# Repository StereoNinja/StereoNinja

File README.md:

# Stereo Ninja

Stereo Ninja is a DIY digital stereo microscope

# Overview

If you ever soldered SMT components or looked for issues on one of those tiny PCBs, you know that using a good microscope helps a lot, especially if it is a stereo microscope. But a good stereo microscope comes with a hefty price tag, so it's not for everyone. A cheap alternative is using a "usb microscope", but then of course you do not have stereo vision.

Our idea is to combine best of both worlds. Having proper stereoscopic view on your work piece and using relatively cheap digital components for archiving that. If you already have a 3D capable monitor, you only need a pair of cameras with suitable optics and some electronics for combining the two video streams into a single one that your monitor understands. We are using a Raspberry Pi for that (what else? ;-)).

# Details

Stereo Ninja is a dual camera setup for stereoscopic microscopy. The heart of the project is a Raspberry Pi. To be precise, you need a Raspberry Pi 3 or 4 Compute Module and a breakout board that gives you access to both MIPI CSI camera input ports the chip set offers, but is not available at the standard Raspberry Pi 3 or 4 versions. Then of course, you need 2 RaspberryPi-compatible cameras with suitable lenses. Our microscope setup is meant for electronics work, so we chose lenses that do not give you that much of a magnification, but permits an adequate lens-object distance for conveniently working under it. Then of course, you need a 3D monitor for displaying the stereoscopic view on your workpiece. We chose a fast 3D-capable gaming monitor with shutter goggles. Finally, a nice stand for you camera is needed.

All these components allow a selection from a variety of choices. We'll try to come up with a good recommendation on what you would want to get, but it is also possible to mix and match these parts (makes sense e.g. when you already own e.g. a 3d monitor). We'll try to list many of these combinations and document how to get them working. If you try a new lens/camera/board/monitor, let us know how it worked for you!

Here's Uli giving you a quick demo of the Stereo Ninja:

# Where do I get more information?

This repository is work in progress. More info about what we did so far can be found on [hackaday.io](https://hackaday.io/project/180044-stereo-ninja)

# Roadmap

## Beta release (work in progress)

* Hardware: 
  * Raspberry Pi CM4, Waveshare CM IO Board
  * 2x Raspberry Pi v1 camera + custom lens
  * connection of camera module with Pi with single cable 
* Software
  * Special version of raspivid
  * Outputs side-by-side stereo mode video to be used with 3d monitor
  * User can switch view (digital zoom on/off)
* Documentation
  * BOM
  * Assembly guide

### Todos Beta Release

- [x] Proof-of-Concept: StereoPi + Raspi3 Compute Module: real-time video stream to 3d monitor
- [x] Tests with CM4 (Raspi4 Compute Module)
- [x] Camera module: Dual-camera mount and enclosure (3d printed)
- [x] Camera module: print + test
- [x] Choose cable type for camera module to Pi connection
- [x] Camera board: circuit design 
- [x] Camera board: PCB layout
- [x] Camera board: assembly + testing
- [ ] Finalize Bill of Material
- [ ] Assembly guide / setup instructions

### Todos Release

- [ ] Software: switching between mode 5 (full sensor) and mode 1 (digital zoom)
- [ ] latency optimization: test different software setups, measure latency
- [ ] Select more suitable lenses

## Future feature ideas

* integrate LED lighting
* add buttons e.g. for zooing at camera
* Evaluate possibility the use of standard (non 3D) monitors by generating the signals for the shutter glasses ourselves
* Integrate polarization filter
* software: enable highres photo snapshots
* software: enable streaming/recording
* try to use Raspi v2 compatible cameras (3rd party IMX219 cam with M12 lens mount), see [issue #1](https://github.com/StereoNinja/StereoNinja/issues/1)
* try to use Raspi HQ compatible cameras (3rd party IMX477 cam with M12 lens mount), see [issue #2](https://github.com/StereoNinja/StereoNinja/issues/2)
* smart zoom: zoom into region where your solder tip or test lead points to
* enable video overlay (display PCB info like BOM directly on screen)
* Kicad integration 
* AR mode (e.g. for part placement on PCBs, highlighting tracks, etc)

# FAQ

### I want to build one! Where is the BOM etc?

Hang on for a bit longer. We are preparing the first release. We will have a BOM and all the design files you need by then.

### Do I need a 3D monitor?

Yes. At least for the first version. We are planning a side project that would allow using standard monitors by driving shutter glasses with our own control electronics. But no work has been done on this yet.

### How can I contribute?

At the moment the development is done by a team located at the FabLab München. We are currently not prepared for onboarding 
people who cannot join our in-person meetings. But there are some topics where development could be done quite independently, 
e.g. support for standard monitors (see previous FAQ) or software support for the new Raspberry Pi camera infrastructure.
In any case, if you interested in joining efforts, get in touch!

### How can I get in touch with you?

Drop us an email: stereoninja@fablab-muenchen.de

We are also on twitter: https://twitter.com/_stereoninja

---

Stereo Ninja is a project by FabLab München e.V. It is part of the [MakerTools project](https://wiki.fablab-muenchen.de/pages/viewpage.action?pageId=126815075), which is sponsored by the Federal Ministry of Education and Research.

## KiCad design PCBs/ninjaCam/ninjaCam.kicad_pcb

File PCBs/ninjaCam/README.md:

Empty directory for first Version for "ninjaCam" PCB
Use on your own risk - could create some magic smoke or just not working 

Should be pluged on Waveshare's Mini Base Board for Raspberry CM4. See also Mechanical/Cad files for assembly. 

License of PCB in this directory:
CERN-OHL-W

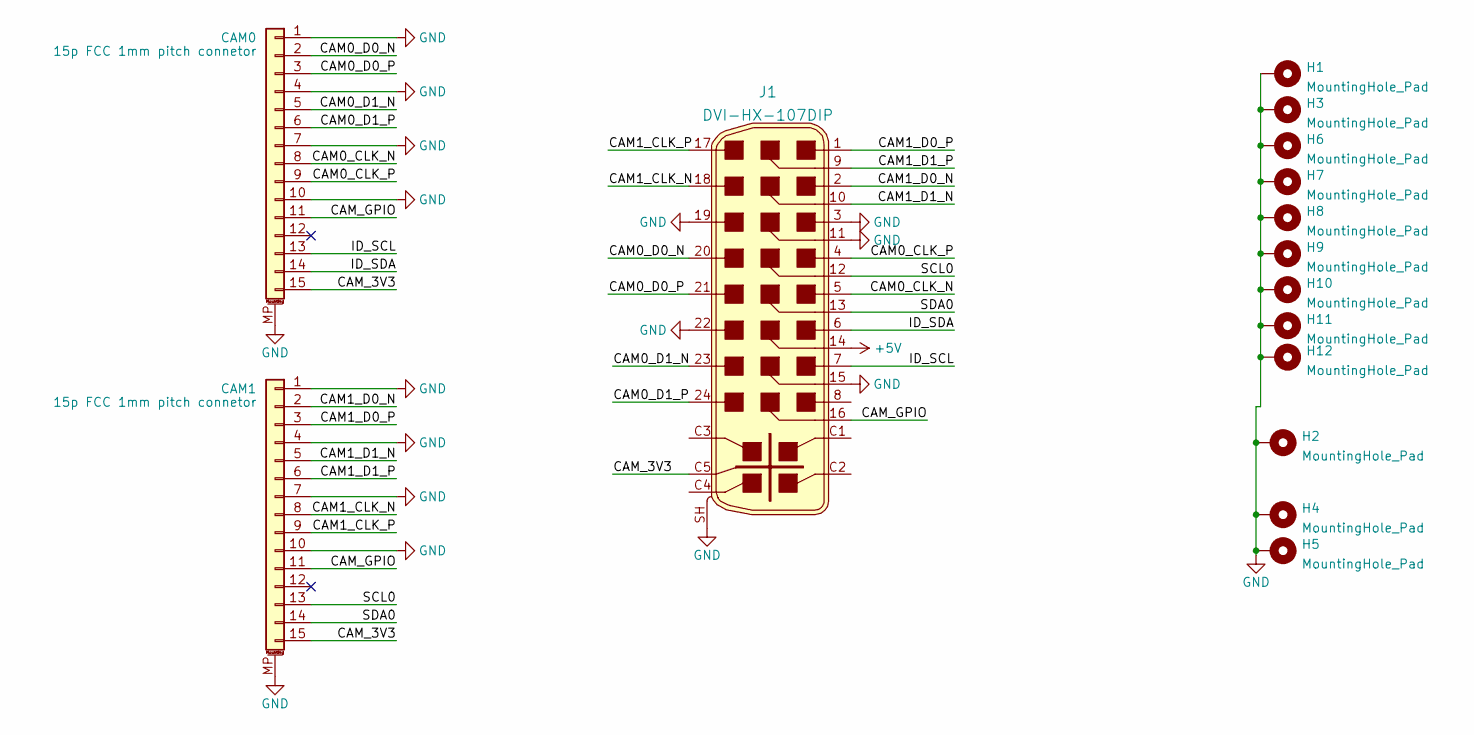
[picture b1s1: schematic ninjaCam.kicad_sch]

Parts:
CAM0, CAM1: 15p FCC 1mm pitch connetor; TE_1-84952-5_1x15-1MP_P1.0mm_Horizontal
H1, H3, H6, H7, H8, H9, H10, H11, H12: MountingHole_Pad; WA-SMSI_9774010360
H2, H4, H5: MountingHole_Pad; MountingHole_3.2mm_M3_Pad_Via
J1: DVI-HX-107DIP; DVI_Female_74320-9010; MPN DVI-HX-107DIP; LCSC# C2936242

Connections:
+5V: J1.14
/CAM0_CLK_N: CAM0.8, J1.5
/CAM0_CLK_P: CAM0.9, J1.4
/CAM0_D0_N: CAM0.2, J1.20
/CAM0_D0_P: CAM0.3, J1.21
/CAM0_D1_N: CAM0.5, J1.23
/CAM0_D1_P: CAM0.6, J1.24
/CAM1_CLK_N: CAM1.8, J1.18
/CAM1_CLK_P: CAM1.9, J1.17
/CAM1_D0_N: CAM1.2, J1.2
/CAM1_D0_P: CAM1.3, J1.1
/CAM1_D1_N: CAM1.5, J1.10
/CAM1_D1_P: CAM1.6, J1.9
/CAM_3V3: CAM0.15, CAM1.15, J1.C5
/CAM_GPIO: CAM0.11, CAM1.11, J1.16
/ID_SCL: CAM0.13, J1.7
/ID_SDA: CAM0.14, J1.6
/SCL0: CAM1.13, J1.12
/SDA0: CAM1.14, J1.13
GND: CAM0.1, CAM0.4, CAM0.7, CAM0.10, CAM0.MP (MountPin), CAM1.1, CAM1.4, CAM1.7, CAM1.10, CAM1.MP (MountPin), H1.1, H2.1, H3.1, H4.1, H5.1, H6.1, H7.1, H8.1, H9.1, H10.1, H11.1, H12.1, J1.3, J1.11, J1.15, J1.19, J1.22, J1.SH

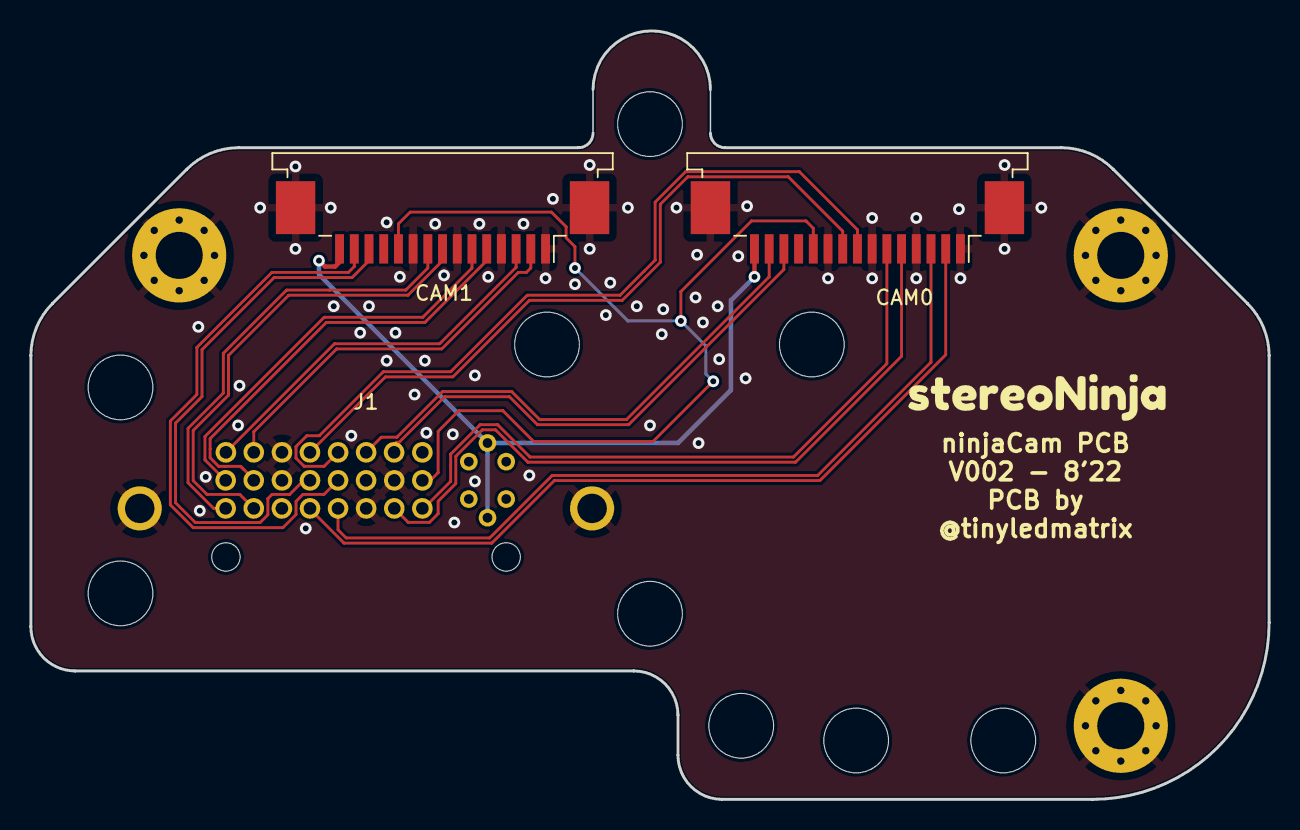
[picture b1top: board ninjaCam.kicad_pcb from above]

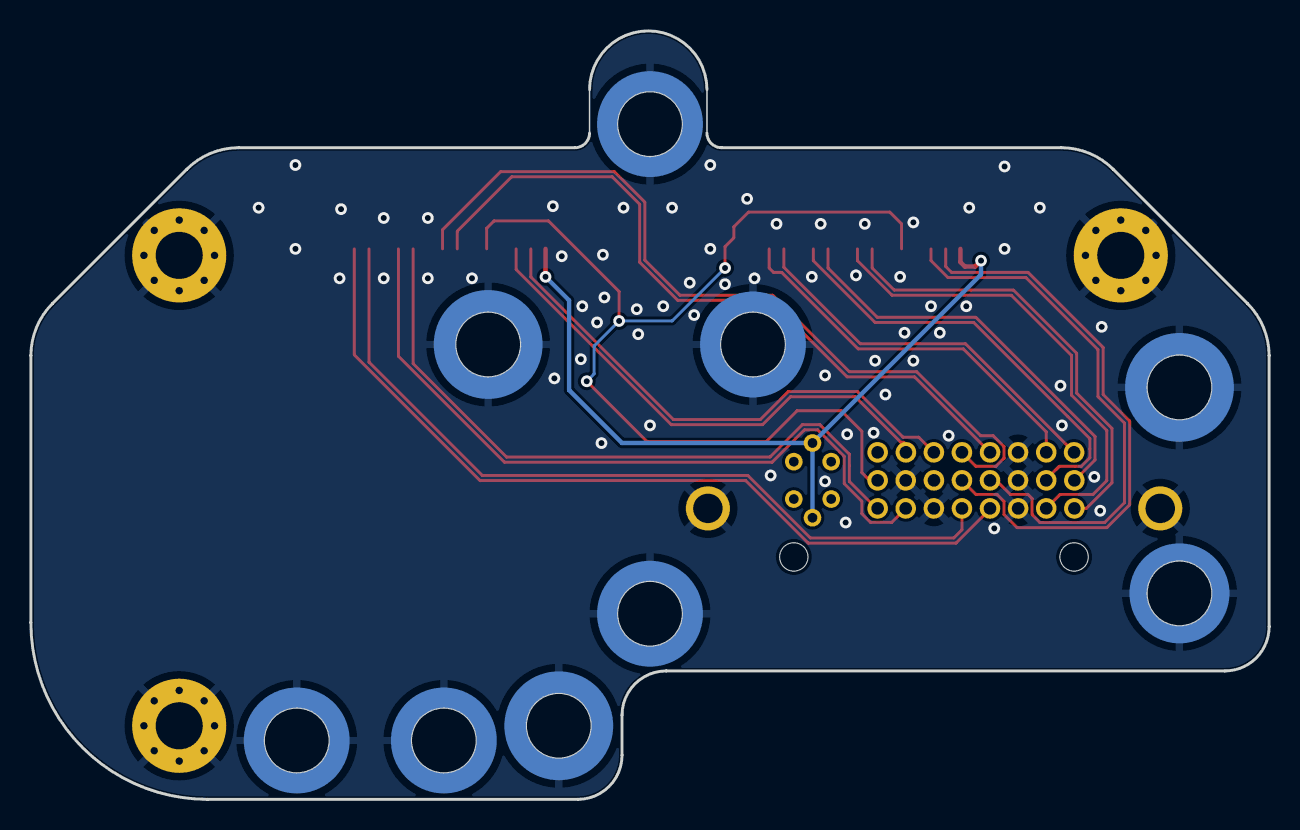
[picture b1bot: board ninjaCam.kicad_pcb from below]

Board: 2 copper layers, 84.2 x 52.2 mm, 16 parts (9 on the bottom side), 19 nets.

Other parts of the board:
kibuzzard-62BCCBE5: G***; kibuzzard-62BCCBE5

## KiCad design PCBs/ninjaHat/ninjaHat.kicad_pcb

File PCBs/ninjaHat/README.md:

Untested first Version for "ninjaHat" PCB
Use on your own risk - could create some magic smoke or just not working 

Should be pluged on Waveshare's Mini Base Board for Raspberry CM4. See also Mechanical/Cad files for assembly. 

License of PCB in this directory:
CERN-OHL-W

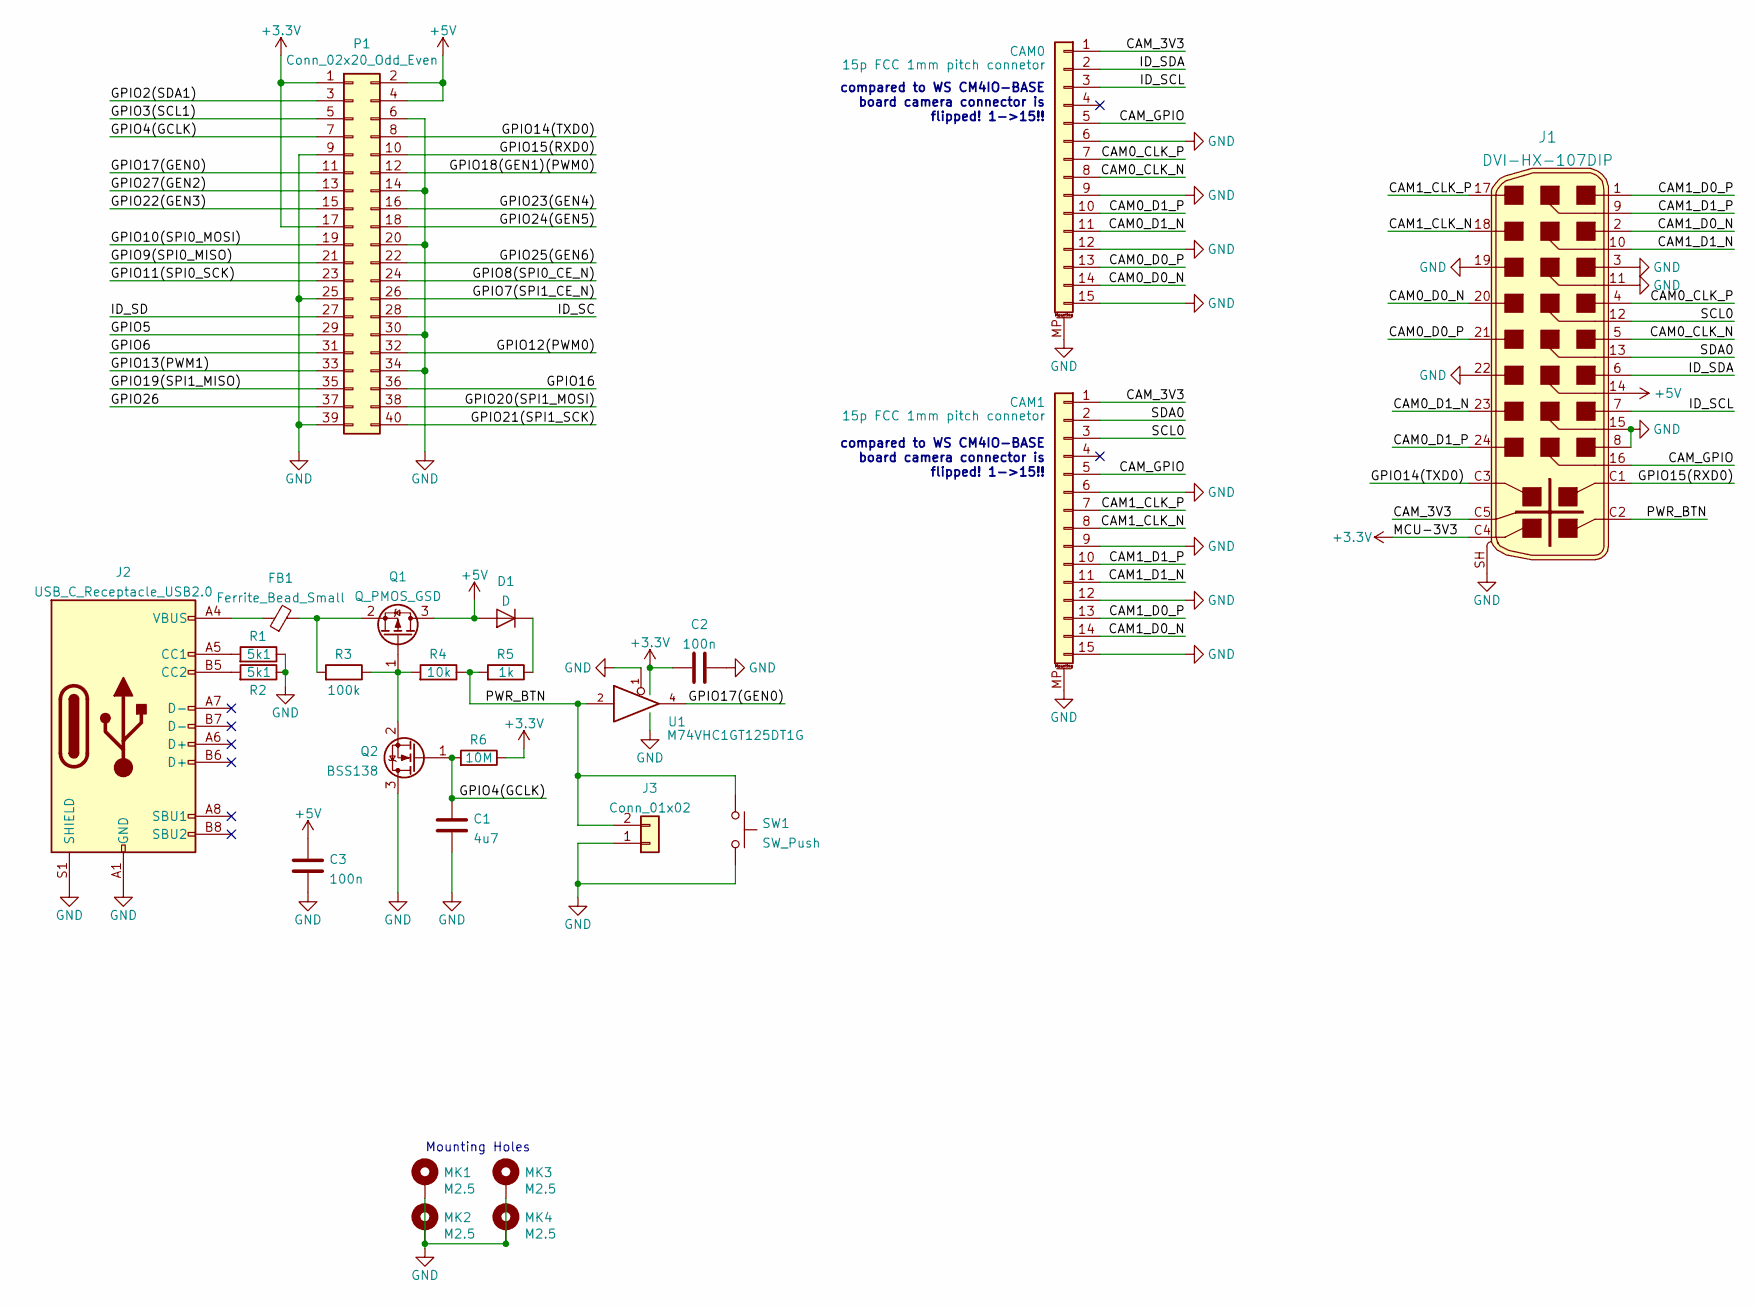
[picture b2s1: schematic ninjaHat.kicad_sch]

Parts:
C1: 4u7; C_0603_min
C2, C3: 100n; C_0603_min
CAM0, CAM1: 15p FCC 1mm pitch connetor; TE_1-84952-5_1x15-1MP_P1.0mm_Horizontal
D1: D; D_SOD-323
FB1: Ferrite_Bead_Small; L_0603_min
J1: DVI-HX-107DIP; DVI_Female_74320-9010; MPN DVI-HX-107DIP; LCSC# C2936242
J2: USB_C_Receptacle_USB2.0; USB_C_Receptacle_GT-USB-7010
J3: Conn_01x02; PinHeader_1x02_P2.54mm_Vertical
MK1, MK2, MK3, MK4: M2.5; MountingHole_3.2mm_M3_Pad_Via
P1: Conn_02x20_Odd_Even; PinSocket_2x20_P2.54mm_Vertical
Q1: Q_PMOS_GSD; SOT-23
Q2: BSS138; SOT-23
R1, R2: 5k1; R_0603_min
R3: 100k; R_0603_min
R4: 10k; R_0603_min
R5: 1k; R_0603_min
R6: 10M; R_0603_min
SW1: SW_Push; SW_PUSH_6mm
U1: M74VHC1GT125DT1G; TSOP-5_1.65x3.05mm_P0.95mm

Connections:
+3V3: C2.1, J1.C4, P1.1, P1.17, R6.1, U1.5 (VCC)
+5V: C3.2, D1.2 (A), J1.14, P1.2, P1.4, Q1.3 (D)
/CAM0_CLK_N: CAM0.8, J1.5
/CAM0_CLK_P: CAM0.7, J1.4
/CAM0_D0_N: CAM0.14, J1.20
/CAM0_D0_P: CAM0.13, J1.21
/CAM0_D1_N: CAM0.11, J1.23
/CAM0_D1_P: CAM0.10, J1.24
/CAM1_CLK_N: CAM1.8, J1.18
/CAM1_CLK_P: CAM1.7, J1.17
/CAM1_D0_N: CAM1.14, J1.2
/CAM1_D0_P: CAM1.13, J1.1
/CAM1_D1_N: CAM1.11, J1.10
/CAM1_D1_P: CAM1.10, J1.9
/CAM_3V3: CAM0.1, CAM1.1, J1.C5
/CAM_GPIO: CAM0.5, CAM1.5, J1.16
/GPIO2(SDA1): P1.3
/GPIO3(SCL1): P1.5
/GPIO4(GCLK): C1.1, P1.7, Q2.1 (G), R6.2
/GPIO5: P1.29
/GPIO6: P1.31
/GPIO7(SPI1_CE_N): P1.26
/GPIO8(SPI0_CE_N): P1.24
/GPIO9(SPI0_MISO): P1.21
/GPIO10(SPI0_MOSI): P1.19
/GPIO11(SPI0_SCK): P1.23
/GPIO12(PWM0): P1.32
/GPIO13(PWM1): P1.33
/GPIO14(TXD0): J1.C3, P1.8
/GPIO15(RXD0): J1.C1, P1.10
/GPIO16: P1.36
/GPIO17(GEN0): P1.11, U1.4
/GPIO18(GEN1)(PWM0): P1.12
/GPIO19(SPI1_MISO): P1.35
/GPIO20(SPI1_MOSI): P1.38
/GPIO21(SPI1_SCK): P1.40
/GPIO22(GEN3): P1.15
/GPIO23(GEN4): P1.16
/GPIO24(GEN5): P1.18
/GPIO25(GEN6): P1.22
/GPIO26: P1.37
/GPIO27(GEN2): P1.13
/ID_SC: P1.28
/ID_SCL: CAM0.3, J1.7
/ID_SD: P1.27
/ID_SDA: CAM0.2, J1.6
/PWR_BTN: J1.C2, J3.2, R4.1, R5.2, SW1.1, U1.2
/SCL0: CAM1.3, J1.12
/SDA0: CAM1.2, J1.13
GND: C1.2, C2.2, C3.1, CAM0.6, CAM0.9, CAM0.12, CAM0.15, CAM0.MP (MountPin), CAM1.6, CAM1.9, CAM1.12, CAM1.15, CAM1.MP (MountPin), J1.3, J1.8, J1.11, J1.15, J1.19, J1.22, J1.SH, J2.A1 (GND), J2.A12 (GND), J2.B1 (GND), J2.B12 (GND), J2.S1 (SHIELD), J3.1, MK1.1, MK2.1, MK3.1, MK4.1, P1.6, P1.9, P1.14, P1.20, P1.25, P1.30, P1.34, P1.39, Q2.3 (D), R1.1, R2.1, SW1.2, U1.1, U1.3 (GND)
unnamed: D1.1 (K), R5.1
unnamed: FB1.1, J2.A4 (VBUS), J2.A9 (VBUS), J2.B4 (VBUS), J2.B9 (VBUS)
unnamed: FB1.2, Q1.2 (S), R3.2
unnamed: J2.A5 (CC1), R1.2
unnamed: J2.B5 (CC2), R2.2
unnamed: Q1.1 (G), Q2.2 (S), R3.1, R4.2

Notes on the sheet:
compared to WS CM4IO-BASE board camera connector is flipped! 1->15!!
Mounting Holes

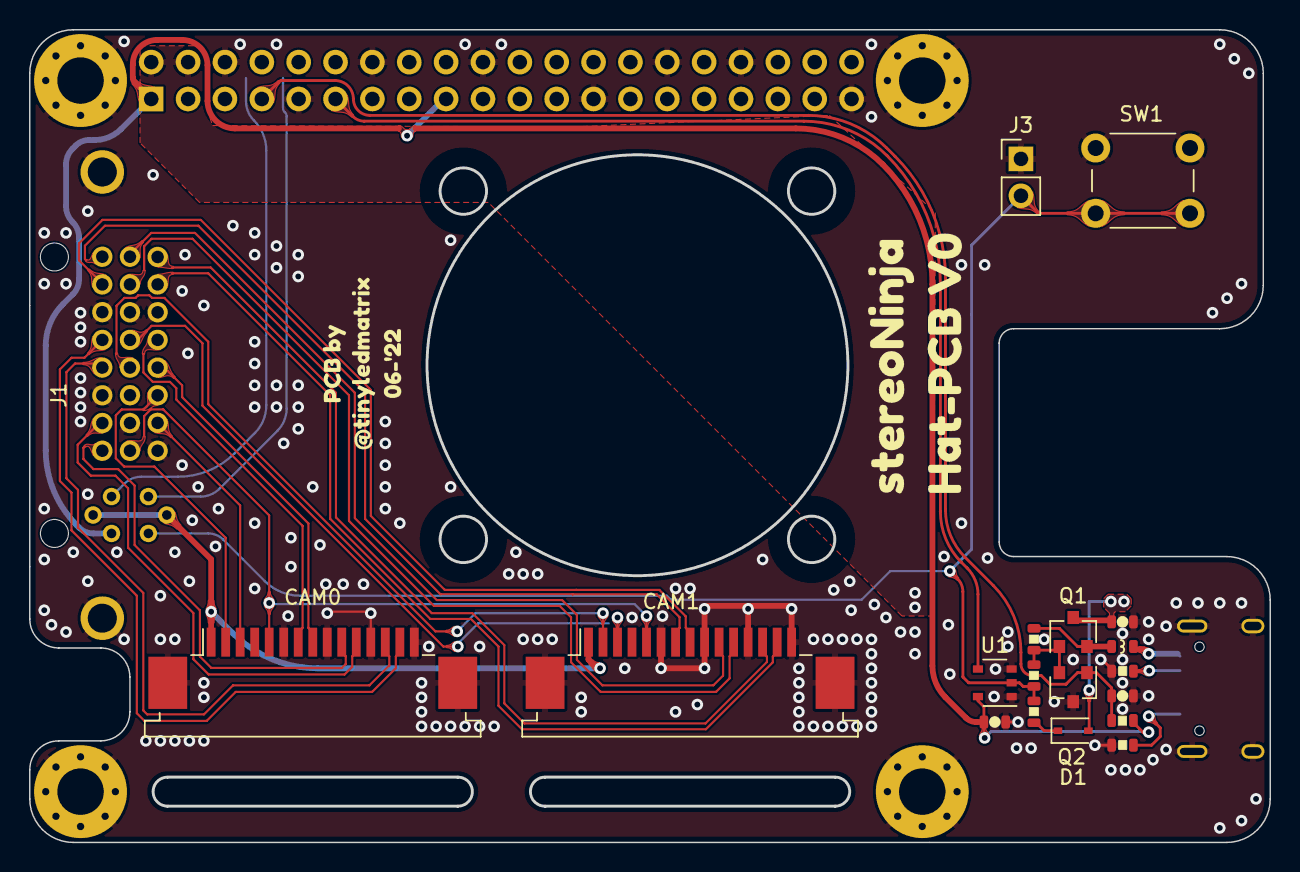
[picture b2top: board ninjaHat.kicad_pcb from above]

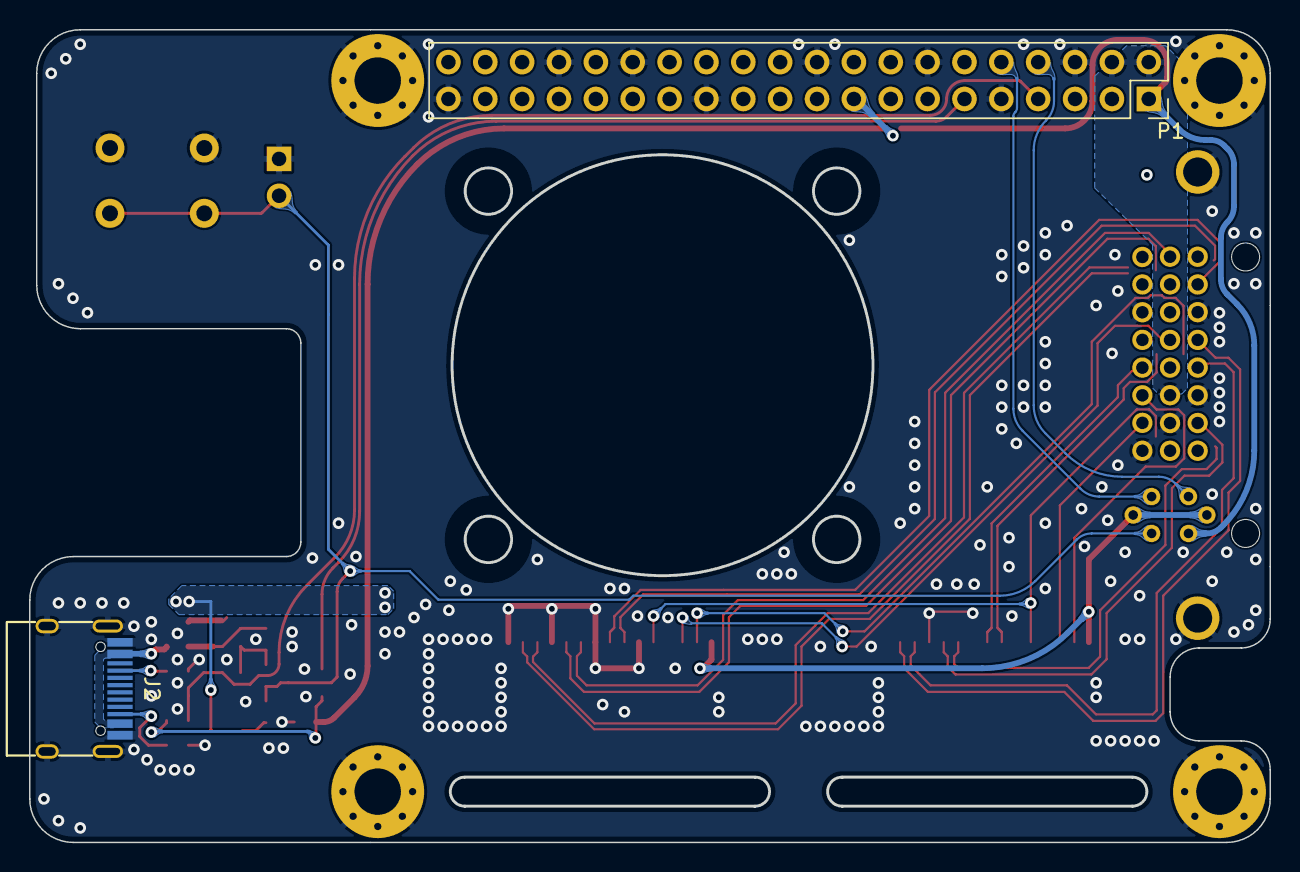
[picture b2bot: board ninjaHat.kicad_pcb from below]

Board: 2 copper layers, 85.4 x 55.9 mm, 29 parts (2 on the bottom side), 32 nets.

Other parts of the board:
kibuzzard-62A7984C: G***; kibuzzard-62A7984C
kibuzzard-62A79922: G***; kibuzzard-62A79922
kibuzzard-62A79934: G***; kibuzzard-62A79934
kibuzzard-62A79947: G***; kibuzzard-62A79947

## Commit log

2022-05-06 initial readme (+images)
2022-05-06 Update README.md
    fix md formatting
2022-05-06 make images smaller (too big for readme)
2022-05-13 added files for 3d printing
2022-05-19 Better milestone definition, updated todos
2022-05-19 updated Future feature ideas section
2022-05-19 Update README.md
    added links to issues #1 and #2 (test v2 and HQ cams)
2022-06-25 Added PCB kicad files for HAT-PCB
    see also readme
2022-06-25 fixed typo
2022-06-25 prepared empty directory for upcoming ninjaCAM PCB
2022-06-25 mechanical files for ninjaHat
2022-06-25 fixed markdown typo
2022-06-25 some reorganisation
2022-06-25 added machanical data for eraly draft of camera part
    just for demonstration probably not working good
2022-07-06 removed old files
2022-07-06 added NinjaStand files, Fusion version v10
2022-07-06 added ninjaCam STL files
2022-07-06 more screenshots of the assembly
2022-07-06 added FAQ
2022-07-06 moved DVI cutout a bit to the left
2022-07-29 Added ninjaCam V002 - untested!
2022-07-30 moved one pair of mounting holes (for cam holder) to be x=50mm y=10mm relative to other cam holder mounting hole
2022-07-30 updated pcb render
2022-08-01 updated gitignore
2022-08-01 added schematic as png
2022-08-04 New camholders
2022-08-04 Additional Files for printing Laser cutting
2022-08-04 connected pin8 of VGa to GND was NC before
    on hat/fpga also connected to gnd
2023-04-27 update title img
